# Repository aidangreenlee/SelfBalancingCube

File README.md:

# SelfBalancingCube

The greatest cube to ever do it

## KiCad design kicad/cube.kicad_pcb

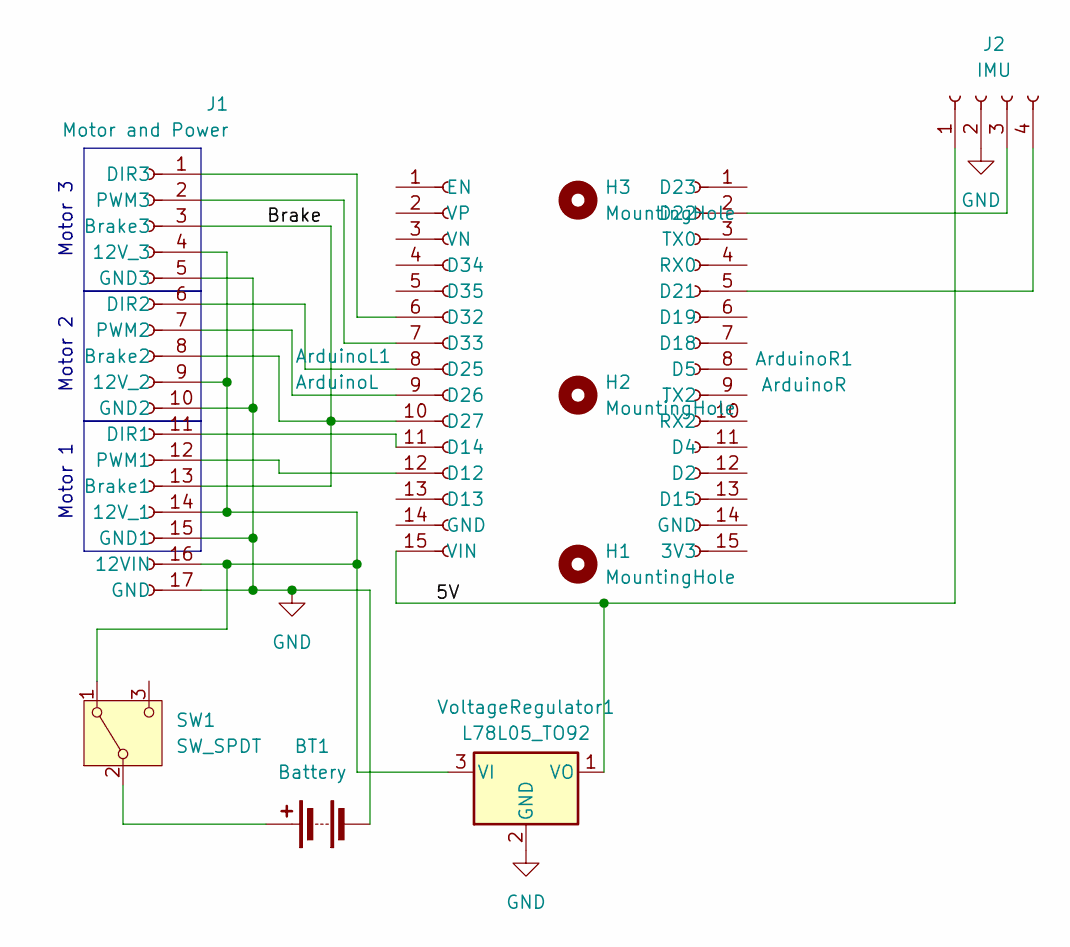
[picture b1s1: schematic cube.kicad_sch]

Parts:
ArduinoL1: ArduinoL; PinSocket_1x15_P2.54mm_Vertical
ArduinoR1: ArduinoR; PinSocket_1x15_P2.54mm_Vertical
BT1: Battery; SolderWirePad_1x02_SMD_1x2mm
H1, H2, H3: MountingHole; MountingHole_3.2mm_M3
J1: Motor and Power; PinSocket_1x17_P2.54mm_Vertical
J2: IMU; PinSocket_1x04_P2.54mm_Vertical
SW1: SW_SPDT; PinSocket_1x03_P2.54mm_Vertical
VoltageRegulator1: L78L05_TO92; TO-92_Inline

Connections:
/5V: ArduinoL1.15 (VIN), J2.1, VoltageRegulator1.1 (VO)
/Brake: ArduinoL1.10 (D27), J1.3 (Brake3), J1.8 (Brake2), J1.13 (Brake1)
GND: BT1.2 (-), J1.5 (GND3), J1.10 (GND2), J1.15 (GND1), J1.17 (GND), J2.2, VoltageRegulator1.2 (GND)
unnamed: ArduinoL1.12 (D12), J1.12 (PWM1)
unnamed: ArduinoL1.11 (D14), J1.11 (DIR1)
unnamed: ArduinoL1.8 (D25), J1.6 (DIR2)
unnamed: ArduinoL1.9 (D26), J1.7 (PWM2)
unnamed: ArduinoL1.6 (D32), J1.1 (DIR3)
unnamed: ArduinoL1.7 (D33), J1.2 (PWM3)
unnamed: ArduinoR1.5 (D21), J2.4
unnamed: ArduinoR1.2 (D22), J2.3
unnamed: BT1.1 (+), SW1.2 (B)
unnamed: J1.4 (12V_3), J1.9 (12V_2), J1.14 (12V_1), J1.16 (12VIN), SW1.1 (A), VoltageRegulator1.3 (VI)

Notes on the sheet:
Motor 1
Motor 2
Motor 3

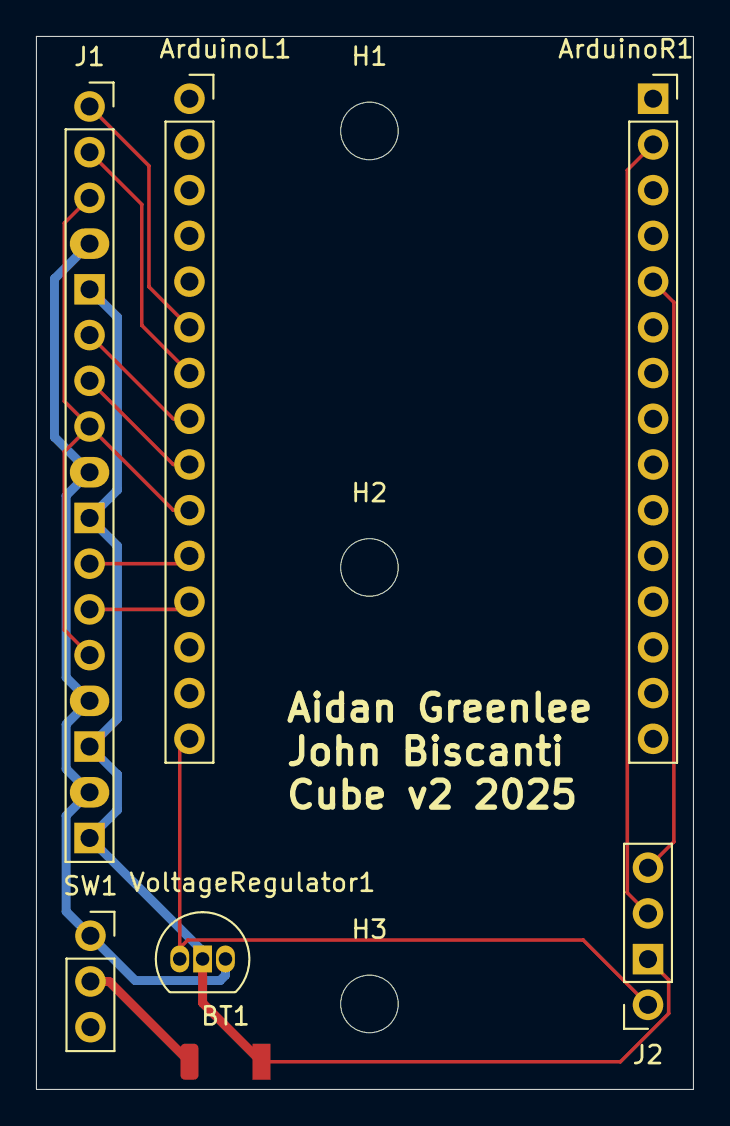
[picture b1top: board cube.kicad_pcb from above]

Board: 2 copper layers, 36.5 x 58.5 mm, 10 parts (0 on the bottom side), 13 nets.

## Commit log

2024-03-06 initial motor setup
2024-03-09 Update README.md
    Important README update
2024-03-10 added imu and filtering code
2024-03-10 Update motor.ino
    Adding PID structure
2024-03-15 Added calibration framework
2024-03-21 adding pid code for single axis
2024-03-24 added gyro to PID
2024-03-26 Adding updates form class 3/25
2024-03-30 adding solidworks parts and assembly
2024-03-30 adding nidec assembly
2024-04-01 memory allocation changes - does not fix bug
2024-04-04 BLDC motor test
2024-04-10 Updated files to work with ESP32.
2024-04-26 adding bluetooth setup, motor changes.
2024-05-02 aidans goated coding
2024-05-02 adding sender code
2024-05-05 code from 5/5
2024-05-06 RGB disco party rave
2025-05-11 Adding directory for new setup
2025-05-11 test
2025-07-01 kicad files added
2025-07-01 added pcb stl
